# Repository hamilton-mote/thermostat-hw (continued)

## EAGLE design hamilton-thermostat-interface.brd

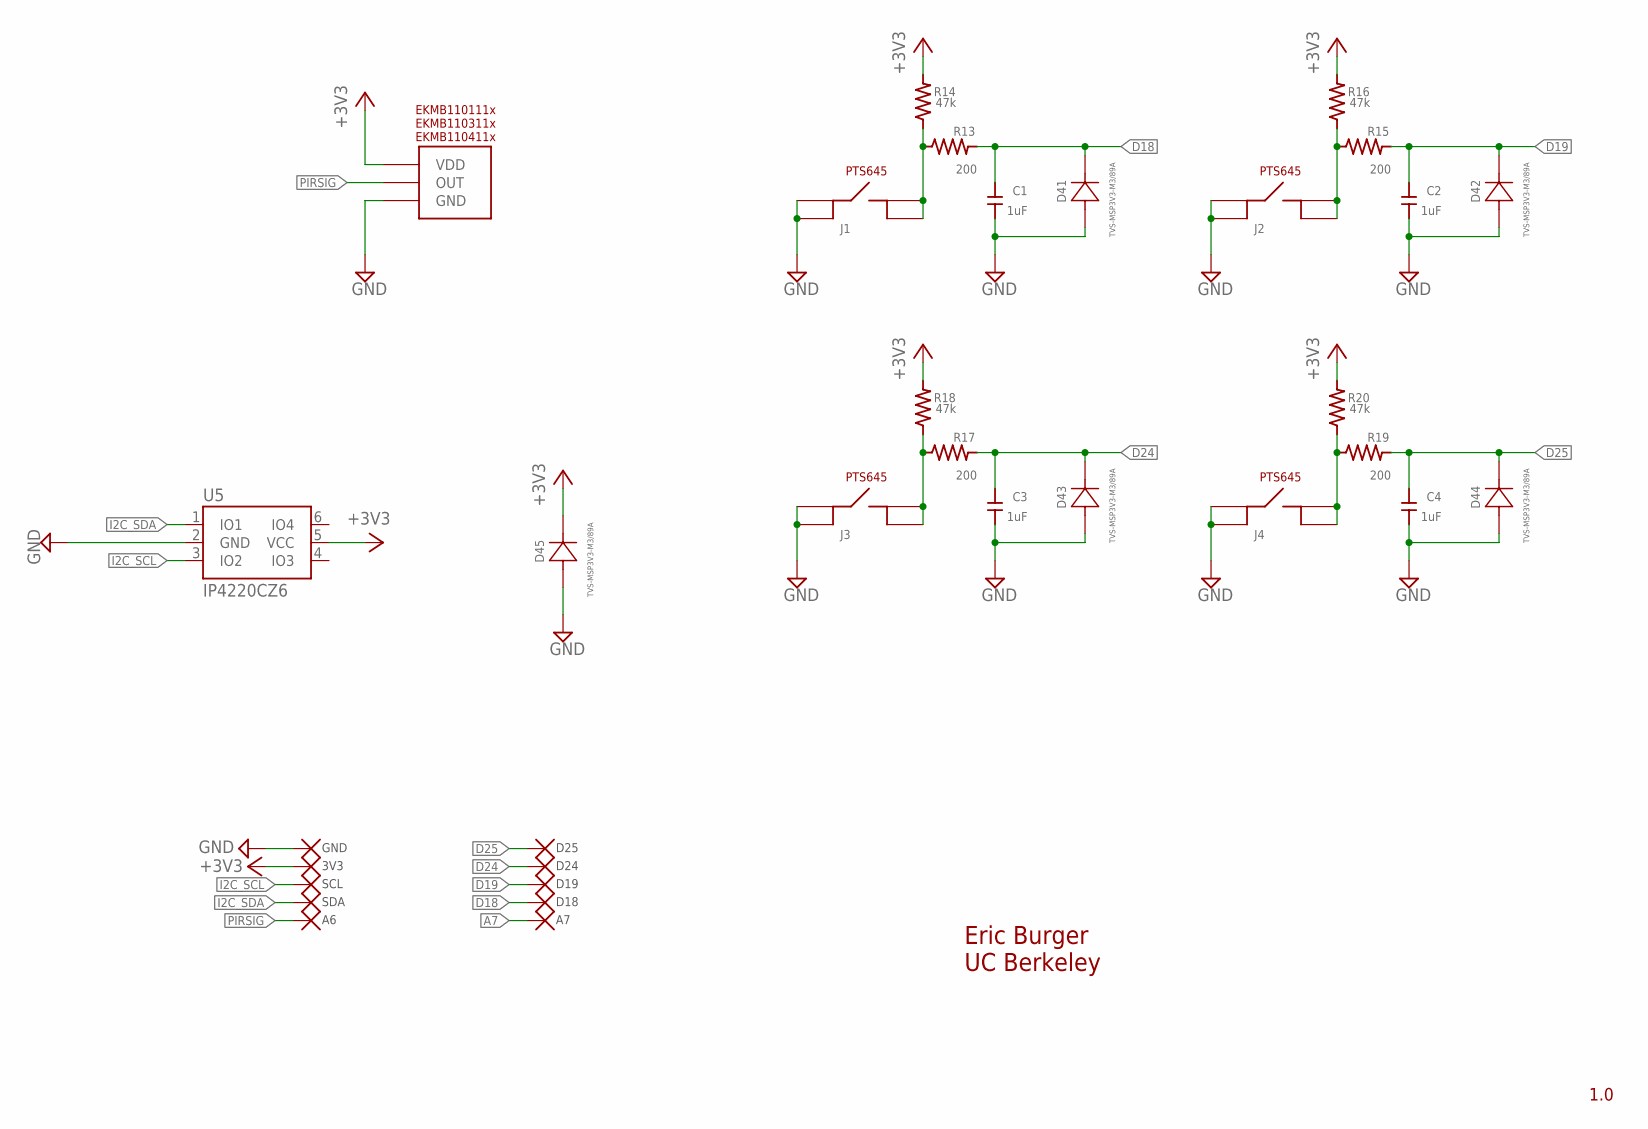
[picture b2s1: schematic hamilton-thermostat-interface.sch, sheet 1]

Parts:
C1, C2, C3, C4: 1uF; S0402
D41, D42, D43, D44, D45: TVS-MSP3V3-M3/89A; DIODE_MSP3V3
J1, J2, J3, J4: PTS645
R13, R15, R17, R19: 200; S0402
R14, R16, R18, R20: 47k; S0402
TP9: SDA; TPP
TP10: SCL; TPP
TP11: 3V3; TPP
TP12: GND; TPP
TP14: D25; TPP
TP15: D24; TPP
TP16: A6; TPP
TP17: D18; TPP
TP18: D19; TPP
TP19: A7; TPP
U4: PANASONIC_PIR; PIR
U5: IP4220CZ6; SOT23-6

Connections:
+3V3: D45.1 (12), R14.P$1, R16.P$1, R18.P$1, R20.P$1, TP11.P$1, U4.VDD, U5.5 (VCC); also elsewhere on the board
A7: TP19.P$1
D18: C1.P$2, D41.1 (12), R13.P$1, TP17.P$1
D19: C2.P$2, D42.1 (12), R15.P$1, TP18.P$1
D24: C3.P$2, D43.1 (12), R17.P$1, TP15.P$1
D25: C4.P$2, D44.1 (12), R19.P$1, TP14.P$1
GND: C1.P$1, C2.P$1, C3.P$1, C4.P$1, D41.2 (21), D42.2 (21), D43.2 (21), D44.2 (21), D45.2 (21), J1.3, J1.4, J2.3, J2.4, J3.3, J3.4, J4.3, J4.4, TP12.P$1, U4.GND, U5.2 (GND); also elsewhere on the board
I2C_SCL: TP10.P$1, U5.3 (IO2); also elsewhere on the board
I2C_SDA: TP9.P$1, U5.1 (IO1); also elsewhere on the board
unnamed: J1.1, J1.2, R13.P$2, R14.P$2
unnamed: J2.1, J2.2, R15.P$2, R16.P$2
unnamed: J3.1, J3.2, R17.P$2, R18.P$2
unnamed: J4.1, J4.2, R19.P$2, R20.P$2
PIRSIG: TP16.P$1, U4.OUT

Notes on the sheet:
1.0
Eric Burger UC Berkeley

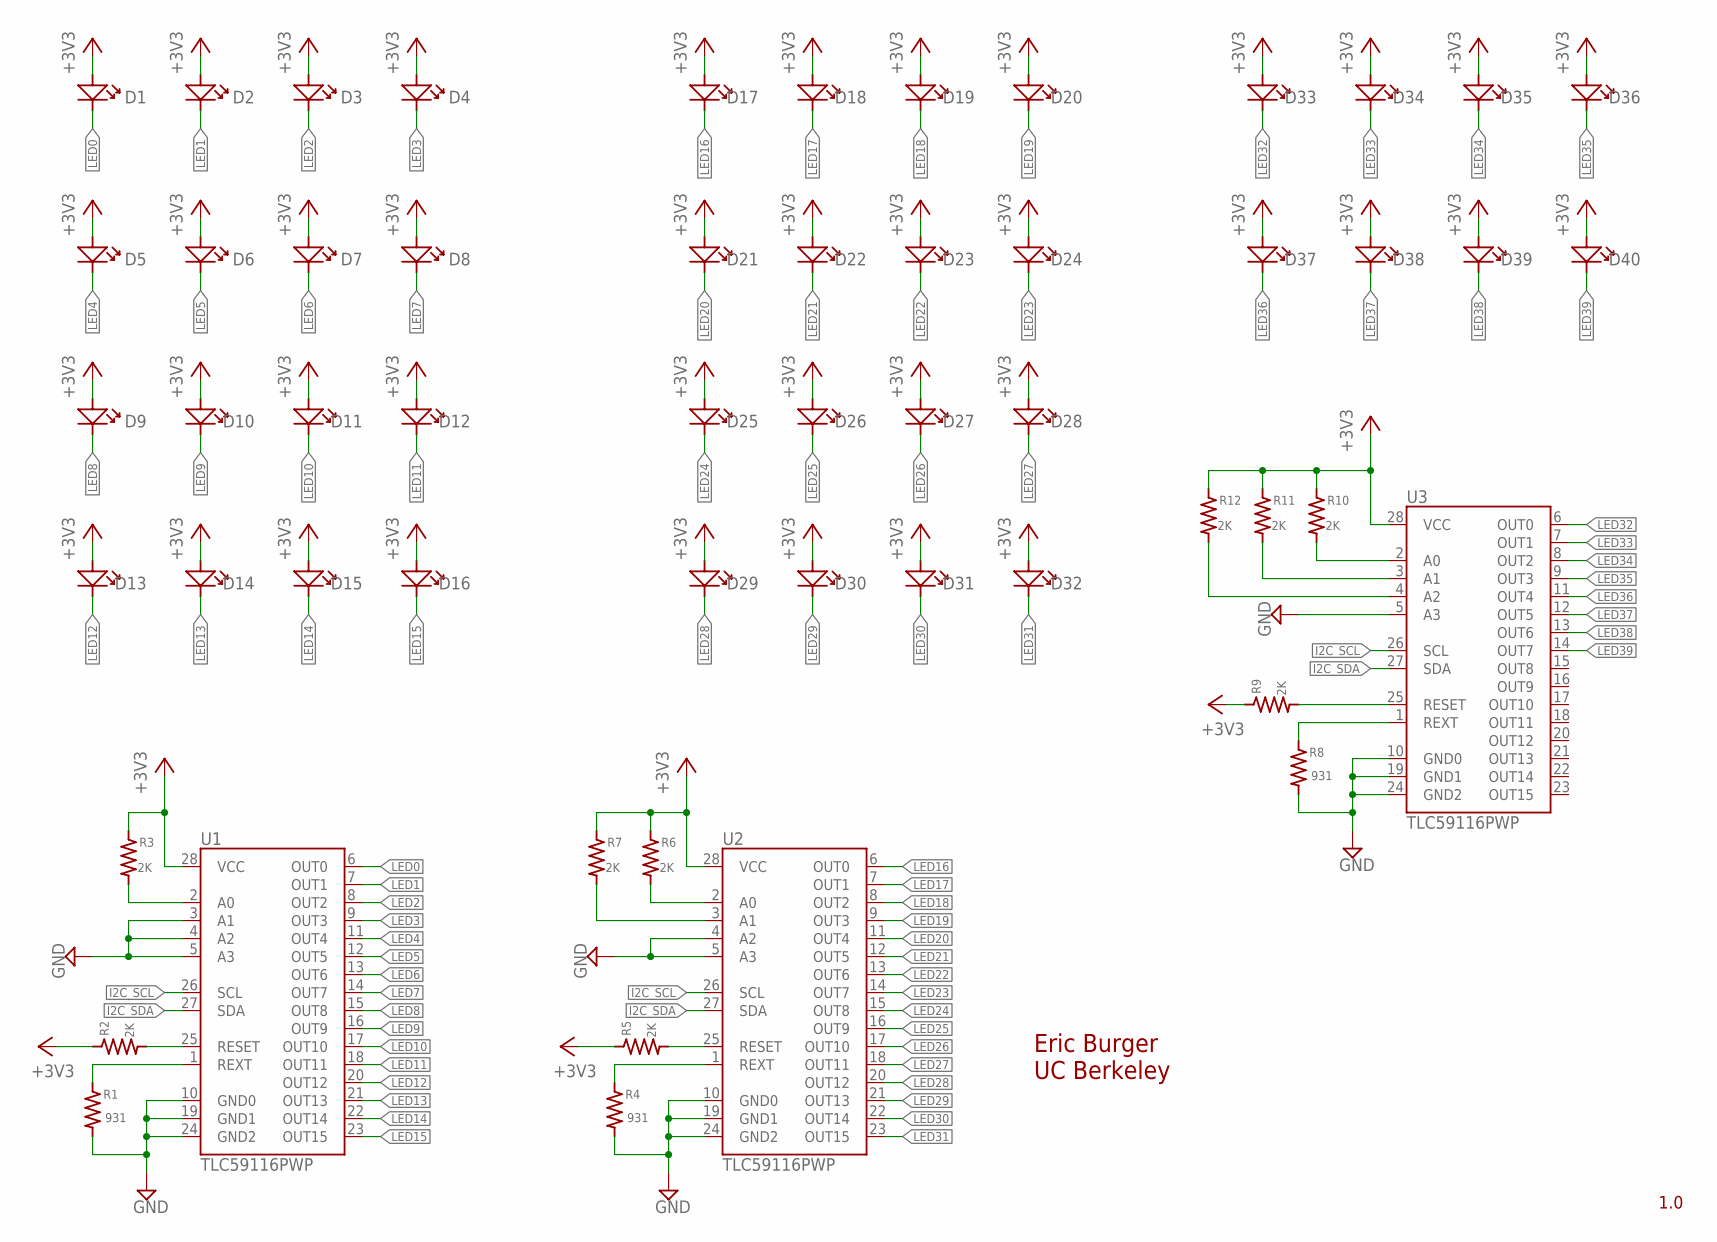
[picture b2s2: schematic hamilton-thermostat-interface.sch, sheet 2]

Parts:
D1, D2, D3, D4, D5, D6, D7, D8, D9, D10, D11, D12, D13, D14, D15, D16, D17, D18, D19, D20, D21, D22, D23, D24, D25, D26, D27, D28, D29, D30, D31, D32, D33, D34, D35, D36, D37, D38, D39, D40: DNP; LINE_0603
R1, R4, R8: 931; S0402
R2, R3, R5, R6, R7, R9, R10, R11, R12: 2K; S0402
U1, U2, U3: TLC59116PWP; TSSOP28-GROUNDPAD

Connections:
+3V3: D1.P (+), D2.P (+), D3.P (+), D4.P (+), D5.P (+), D6.P (+), D7.P (+), D8.P (+), D9.P (+), D10.P (+), D11.P (+), D12.P (+), D13.P (+), D14.P (+), D15.P (+), D16.P (+), D17.P (+), D18.P (+), D19.P (+), D20.P (+), D21.P (+), D22.P (+), D23.P (+), D24.P (+), D25.P (+), D26.P (+), D27.P (+), D28.P (+), D29.P (+), D30.P (+), D31.P (+), D32.P (+), D33.P (+), D34.P (+), D35.P (+), D36.P (+), D37.P (+), D38.P (+), D39.P (+), D40.P (+), R2.P$2, R3.P$2, R5.P$2, R6.P$2, R7.P$2, R9.P$2, R10.P$2, R11.P$2, R12.P$2, U1.28 (VCC), U2.28 (VCC), U3.28 (VCC); also elsewhere on the board
GND: R1.P$1, R4.P$1, R8.P$1, U1.3 (A1), U1.4 (A2), U1.5 (A3), U1.10 (GND0), U1.19 (GND1), U1.24 (GND2), U2.4 (A2), U2.5 (A3), U2.10 (GND0), U2.19 (GND1), U2.24 (GND2), U3.5 (A3), U3.10 (GND0), U3.19 (GND1), U3.24 (GND2); also elsewhere on the board
I2C_SCL: U1.26 (SCL), U2.26 (SCL), U3.26 (SCL); also elsewhere on the board
I2C_SDA: U1.27 (SDA), U2.27 (SDA), U3.27 (SDA); also elsewhere on the board
LED0: D1.N (-), U1.6 (OUT0)
LED1: D2.N (-), U1.7 (OUT1)
LED2: D3.N (-), U1.8 (OUT2)
LED3: D4.N (-), U1.9 (OUT3)
LED4: D5.N (-), U1.11 (OUT4)
LED5: D6.N (-), U1.12 (OUT5)
LED6: D7.N (-), U1.13 (OUT6)
LED7: D8.N (-), U1.14 (OUT7)
LED8: D9.N (-), U1.15 (OUT8)
LED9: D10.N (-), U1.16 (OUT9)
LED10: D11.N (-), U1.17 (OUT10)
LED11: D12.N (-), U1.18 (OUT11)
LED12: D13.N (-), U1.20 (OUT12)
LED13: D14.N (-), U1.21 (OUT13)
LED14: D15.N (-), U1.22 (OUT14)
LED15: D16.N (-), U1.23 (OUT15)
LED16: D17.N (-), U2.6 (OUT0)
LED17: D18.N (-), U2.7 (OUT1)
LED18: D19.N (-), U2.8 (OUT2)
LED19: D20.N (-), U2.9 (OUT3)
LED20: D21.N (-), U2.11 (OUT4)
LED21: D22.N (-), U2.12 (OUT5)
LED22: D23.N (-), U2.13 (OUT6)
LED23: D24.N (-), U2.14 (OUT7)
LED24: D25.N (-), U2.15 (OUT8)
LED25: D26.N (-), U2.16 (OUT9)
LED26: D27.N (-), U2.17 (OUT10)
LED27: D28.N (-), U2.18 (OUT11)
LED28: D29.N (-), U2.20 (OUT12)
LED29: D30.N (-), U2.21 (OUT13)
LED30: D31.N (-), U2.22 (OUT14)
LED31: D32.N (-), U2.23 (OUT15)
LED32: D33.N (-), U3.6 (OUT0)
LED33: D34.N (-), U3.7 (OUT1)
LED34: D35.N (-), U3.8 (OUT2)
LED35: D36.N (-), U3.9 (OUT3)
LED36: D37.N (-), U3.11 (OUT4)
LED37: D38.N (-), U3.12 (OUT5)
LED38: D39.N (-), U3.13 (OUT6)
LED39: D40.N (-), U3.14 (OUT7)
unnamed: R3.P$1, U1.2 (A0)
unnamed: R6.P$1, U2.2 (A0)
unnamed: R4.P$2, U2.1 (REXT)
unnamed: R5.P$1, U2.25 (RESET)
unnamed: R7.P$1, U2.3 (A1)
unnamed: R1.P$2, U1.1 (REXT)
unnamed: R10.P$1, U3.2 (A0)
unnamed: R2.P$1, U1.25 (RESET)
unnamed: R8.P$2, U3.1 (REXT)
unnamed: R9.P$1, U3.25 (RESET)
unnamed: R11.P$1, U3.3 (A1)
unnamed: R12.P$1, U3.4 (A2)

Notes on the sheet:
1.0
Eric Burger UC Berkeley

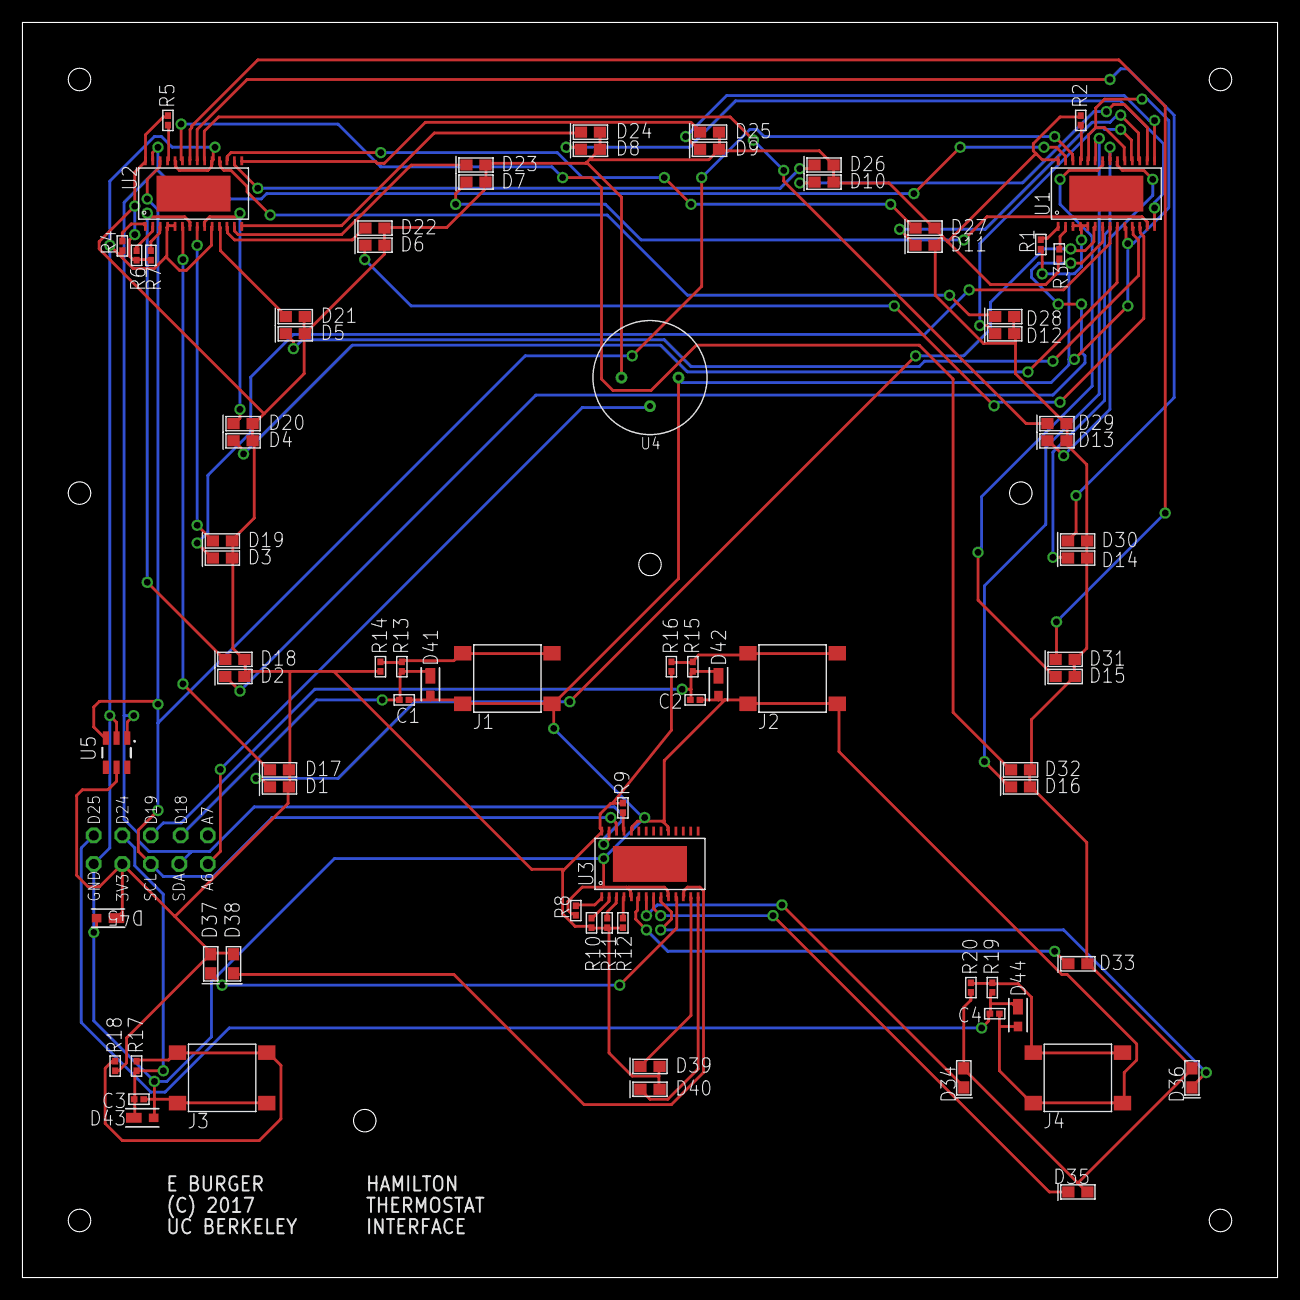
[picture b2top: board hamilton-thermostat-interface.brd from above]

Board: 2 copper layers, 111.8 x 111.8 mm, 88 parts (0 on the bottom side), 65 nets.

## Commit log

2017-04-19 Upload Eagle files
2017-04-28 Add technical details overview
2017-04-29 Move relay jumper location
